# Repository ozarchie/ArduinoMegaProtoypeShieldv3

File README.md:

# ArduinoMegaProtoypeShieldv3
Arduino Mega protoype shield for loading HC05/WiFi modules
Welcome to the ArduinoMegaProtoypeShieldv3 wiki!

# Process
## Used proto_shield_MEGA-REV3 as the starting point
This is the reference schematic and layout from Arduino  
The target board is the arduino Mega2560v3 prototype shield usually supplied with a mini breadboard.  
It is similar to this item:  

I have no relationship with www.robotistan.com  

## Used Eagle 770 to edit schematic and board

The schematic was derived from an actual board.    
The board layout was measured from an actual board.  

<b>There are many points at which errors can be introduced.  
This is NOT a production item and has not been tested.    
It is for experimentation and collaboration only.    
At some stage, it may be 'released' as a verified design.  </b>

## Used eagle2fritzing to create Fritzing part

The part was generated using the eagle2fritzing technique.
See   
https://github.com/fritzing/eagle2fritzing

The program was re-compiled on macOS Sierra and run from the command line.  
`./run.sh ~/Documents/workspace/fritzing-myparts/`

## Minor modification in Fritzing to create and export part

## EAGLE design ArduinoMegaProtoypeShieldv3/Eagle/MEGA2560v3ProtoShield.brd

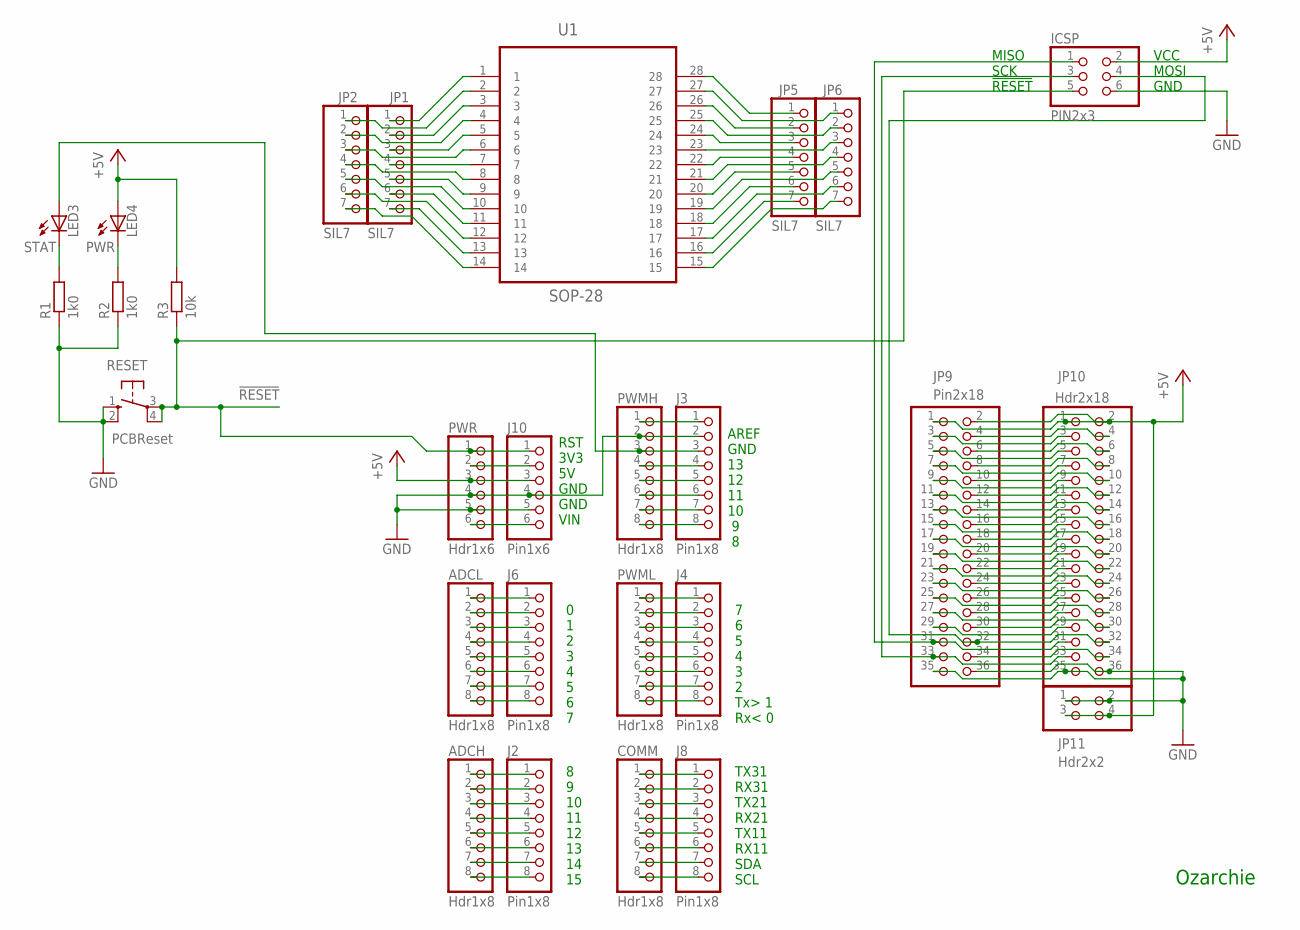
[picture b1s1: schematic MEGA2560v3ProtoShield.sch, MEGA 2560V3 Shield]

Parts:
ADCH: Hdr1x8; 1X08
ADCL: Hdr1x8; 1X08
COMM: Hdr1x8; 1X08
ICSP: PIN2x3; 2X03
J2, J3, J4, J6, J8: Pin1x8; 1X08
J10: Pin1x6; 1X06
JP1, JP2, JP5, JP6: SIL7; 1X07
JP9: Pin2x18; 2X18
JP10: Hdr2x18; 2X18
JP11: Hdr2x2; 2X02
LED3: STAT; CHIPLED_1206
LED4: PWR; CHIPLED_1206
PWMH: Hdr1x8; 1X08
PWML: Hdr1x8; 1X08
PWR: Hdr1x6; 1X06
R1, R2: 1k0; R0805
R3: 10k; R0805
RESET: PCBReset; B3F-10XX
U1: SOP-28; SOP50P1030X264-28N

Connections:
3V3: J10.2, PWR.2
!RESET!: ICSP.5, J10.1, PWR.1, R3.1, RESET.3, RESET.4 (P1)
+5V: ICSP.2, J10.3, JP9.1, JP9.2, JP10.1, JP10.2, JP11.3, JP11.4, LED4.A, PWR.3, R3.2
A0: ADCL.1, J6.1
A1: ADCL.2, J6.2
A2: ADCL.3, J6.3
A3: ADCL.4, J6.4
A4: ADCL.5, J6.5
A5: ADCL.6, J6.6
A6: ADCL.7, J6.7
A7: ADCL.8, J6.8
A8: ADCH.1, J2.1
A9: ADCH.2, J2.2
A10: ADCH.3, J2.3
A11: ADCH.4, J2.4
A12: ADCH.5, J2.5
A13: ADCH.6, J2.6
A14: ADCH.7, J2.7
A15: ADCH.8, J2.8
AREF: J3.1, PWMH.1
D0/RX0: J4.8, PWML.8
D1/TX0: J4.7, PWML.7
D2PWM: J4.6, PWML.6
D3PWM: J4.5, PWML.5
D4PWM: J4.4, PWML.4
D5PWM: J4.3, PWML.3
D6PWM: J4.2, PWML.2
D7PWM: J4.1, PWML.1
D8PWM: J3.8, PWMH.8
D9PWM: J3.7, PWMH.7
D10PWM: J3.6, PWMH.6
D11PWM: J3.5, PWMH.5
D12PWM: J3.4, PWMH.4
D13PWM: J3.3, LED3.A, PWMH.3
D14/TX3: COMM.1, J8.1
D15/RX3: COMM.2, J8.2
D16/TX2: COMM.3, J8.3
D17/RX2: COMM.4, J8.4
D18/TX1: COMM.5, J8.5
D19/RX1: COMM.6, J8.6
D20/SDA: COMM.7, J8.7
D21/SCL: COMM.8, J8.8
D22: JP9.3, JP10.3
D23: JP9.4, JP10.4
D24: JP9.5, JP10.5
D25: JP9.6, JP10.6
D26: JP9.7, JP10.7
D27: JP9.8, JP10.8
D28: JP9.9, JP10.9
D29: JP9.10, JP10.10
D30: JP9.11, JP10.11
D31: JP9.12, JP10.12
D32: JP9.13, JP10.13
D33: JP9.14, JP10.14
D34: JP9.15, JP10.15
D35: JP9.16, JP10.16
D36: JP9.17, JP10.17
D37: JP9.18, JP10.18
D38: JP9.19, JP10.19
D39: JP9.20, JP10.20
D40: JP9.21, JP10.21
D41: JP9.22, JP10.22
D42: JP9.23, JP10.23
D43: JP9.24, JP10.24
D44: JP9.25, JP10.25
D45: JP9.26, JP10.26
D46: JP9.27, JP10.27
D47: JP9.28, JP10.28
D48: JP9.29, JP10.29
D49: JP9.30, JP10.30
D53: JP9.34, JP10.34
GND: ICSP.6, J3.2, J10.4, J10.5, JP9.35, JP9.36, JP10.35, JP10.36, JP11.1, JP11.2, PWMH.2, PWR.4, PWR.5, R1.1, R2.1, RESET.1 (S), RESET.2 (S1)
MISO: ICSP.1, JP9.31, JP10.31
MOSI: ICSP.4, JP9.32, JP10.32
unnamed: LED3.C, R1.2
unnamed: LED4.C, R2.2
SCK: ICSP.3, JP9.33, JP10.33
SO1: JP1.1, U1.1
SO2: JP2.1, U1.2
SO3: JP1.2, U1.3
SO4: JP2.2, U1.4
SO5: JP1.3, U1.5
SO6: JP2.3, U1.6
SO7: JP1.4, U1.7
SO8: JP2.4, U1.8
SO9: JP1.5, U1.9
SO10: JP2.5, U1.10
SO11: JP1.6, U1.11
SO12: JP2.6, U1.12
SO13: JP1.7, U1.13
SO14: JP2.7, U1.14
SO15: JP6.7, U1.15
SO16: JP5.7, U1.16
SO17: JP6.6, U1.17
SO18: JP5.6, U1.18
SO19: JP6.5, U1.19
SO20: JP5.5, U1.20
SO21: JP6.4, U1.21
SO22: JP5.4, U1.22
SO23: JP6.3, U1.23
SO24: JP5.3, U1.24
SO25: JP6.2, U1.25
SO26: JP5.2, U1.26
SO27: JP6.1, U1.27
SO28: JP5.1, U1.28
VIN: J10.6, PWR.6

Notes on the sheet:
RST 3V3 5V GND GND VIN
MISO SCK !RESET!
VCC MOSI GND
AREF GND 13 12 11 10 9 8
7 6 5 4 3 2 Tx> 1 Rx< 0
0 1 2 3 4 5 6 7
8 9 10 11 12 13 14 15
TX31 RX31 TX21 RX21 TX11 RX11 SDA SCL
Ozarchie

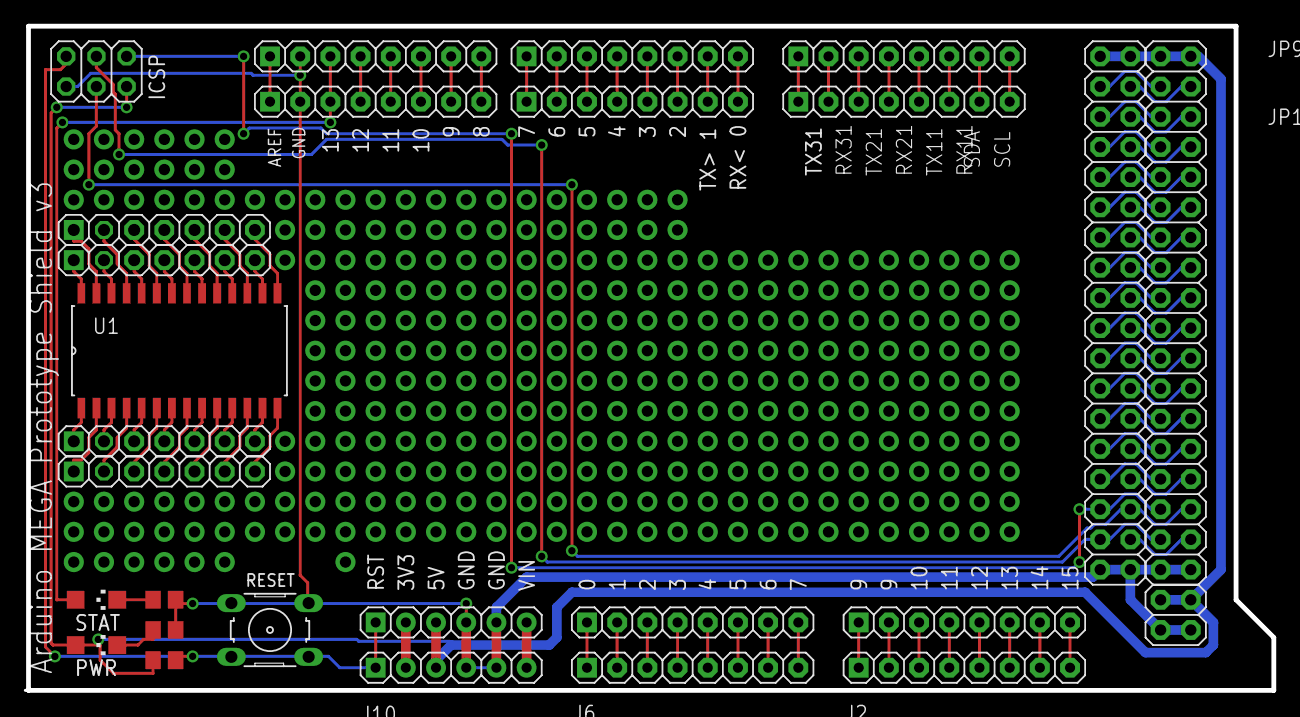
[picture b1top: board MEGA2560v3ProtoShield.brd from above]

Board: 2 copper layers, 104.8 x 55.9 mm, 27 parts (0 on the bottom side), 106 nets.

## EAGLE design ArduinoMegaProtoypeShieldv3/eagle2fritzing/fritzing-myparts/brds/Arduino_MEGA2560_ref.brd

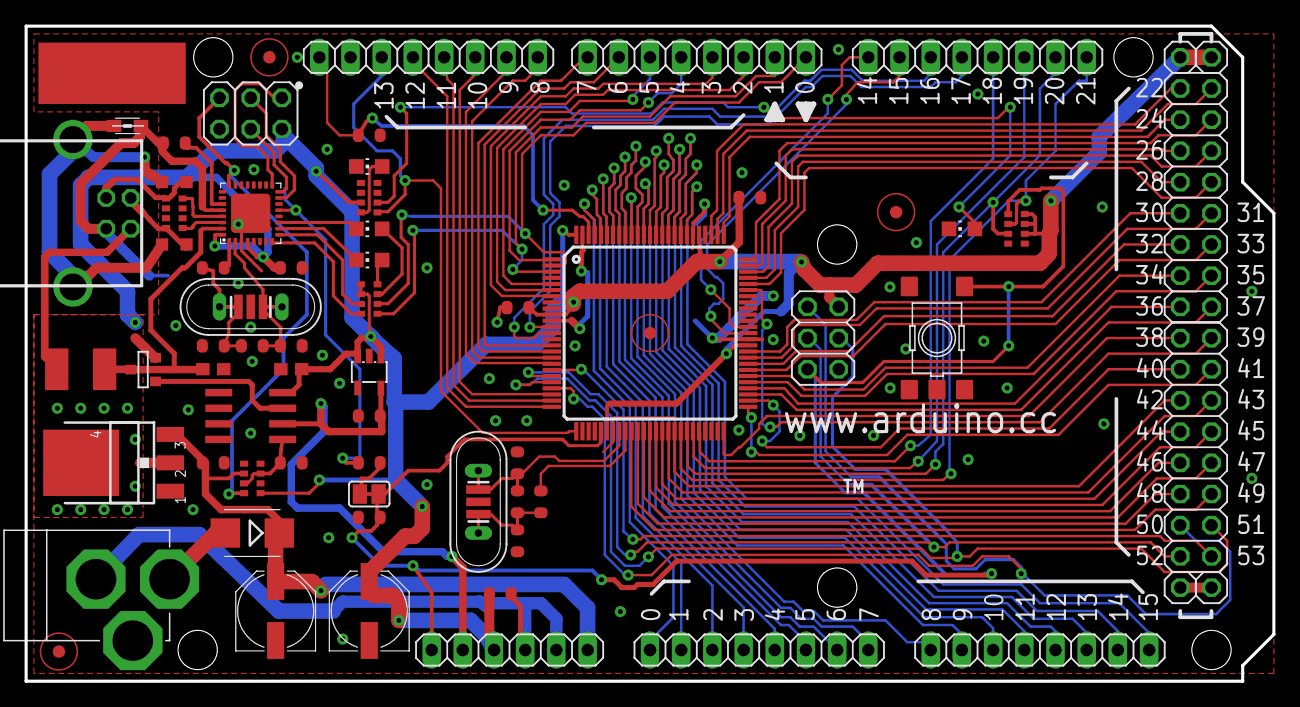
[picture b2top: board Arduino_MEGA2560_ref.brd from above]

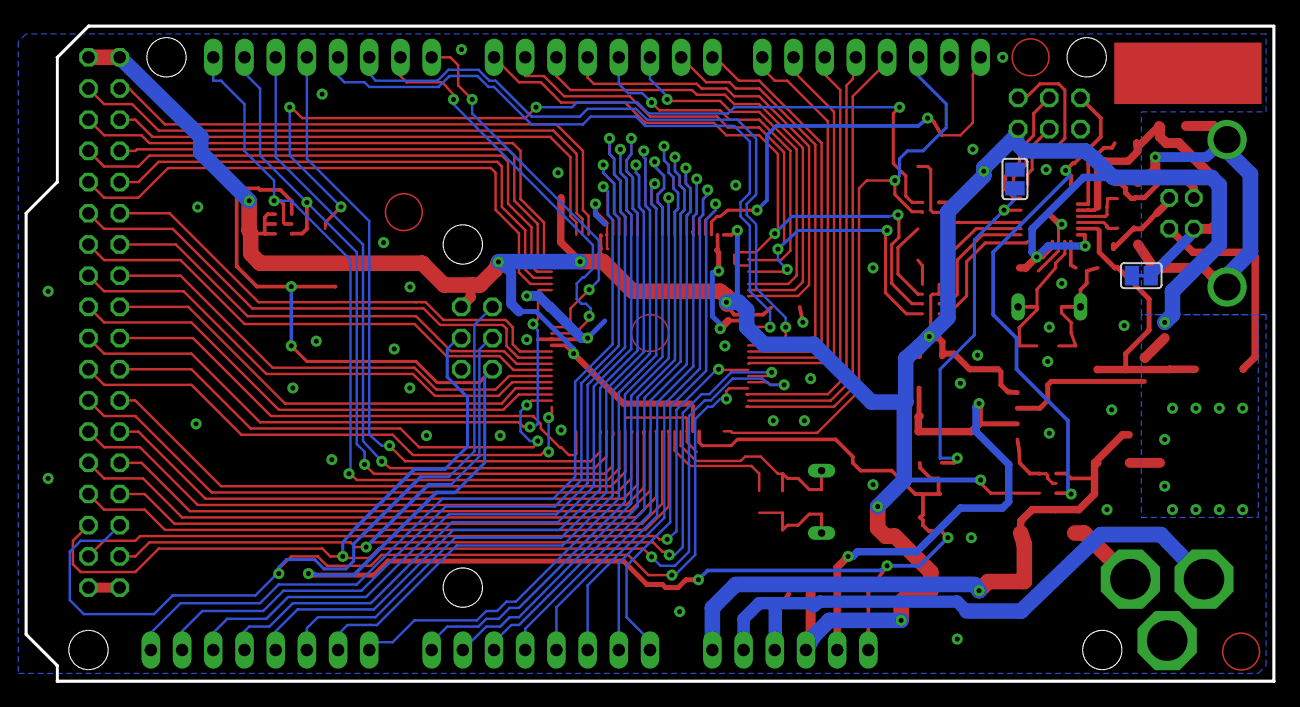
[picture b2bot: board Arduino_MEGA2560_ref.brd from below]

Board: 2 copper layers, 101.6 x 53.3 mm, 72 parts (2 on the bottom side), 107 nets.

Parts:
ADCH: 1X08
ADCL: 1X08
C1, C14, C15, C16, C17: 22p; C0603-ROUND
C2, C3, C4, C5, C6, C7, C9, C12, C13: 100n; C0603-ROUND
C8, C11: 100n; C0603
C10: 1u; C0603-ROUND
COMMUNICATION: 1X08
D1: M7; SMB
F1: 500mA; L1812
GROUND: SJ
IC1: MC33269ST-5.0T3; SOT223
IC2: MC33269D-5.0; DPACK
IC3: ATMEGA2560-16AU; TQFP100
IC4: ATMEGA8U2-MU; QFN32
IC5: LM358D; SO08
IC6: LP2985-33DBVR; SOT23-DBV
ICSP, ICSP1: ICSP; 2X03
JP1, JP2, JP3, JP4: 1X01
L: YELLOW; CHIP-LED0805
L1: BLM21; 0805
ON: GREEN; CHIP-LED0805
PC1, PC2: 47u; PANASONIC_D
POWER: 1X06
PWMH: 1X08
PWML: 1X08
Q1, Q2: 16MHz; QS
R1, R2: 1M; R0603-ROUND
R3, R4: 27R; R0603-ROUND
RESET: TS42
RESET-EN: SJ
RN1, RN5: 10K; CAT16
RN2: 22R; CAY16
RN3, RN4: 1k; CAY16
RX: YELLOW; CHIP-LED0805
T2: FDN340P; SOT-23
TX: YELLOW; CHIP-LED0805
U$2, U$3, U$4, U$5: FIDUCIALMOUNT; FIDUCIA-MOUNT
UBOOT: SJ
X1: DC21MMX; DC-21MM
X2: PN61729
XIOH: 2X08
XIOL: 2X08
Y1, Y2: 16MHz; RESONATOR
Z1, Z2: PGB1010604; CT/CN0603

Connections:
+3V3: C13.2, IC5.6, IC6.5, POWER.2
+5V: C4.1, C5.1, C6.1, C9.1, C11.2, IC1.2, IC1.4, IC2.2, IC3.10, IC3.31, IC3.61, IC3.80, IC3.100, IC4.4, IC4.32, IC5.8, IC6.1, IC6.3, ICSP.2, ICSP1.2, JP1.1, JP2.1, PC2.+, POWER.3, RN1.6, RN1.7, RN1.8, RN3.3, RN4.5, RN4.6, RN5.1, T2.2
ADC0: ADCL.1, IC3.97
ADC1: ADCL.2, IC3.96
ADC2: ADCL.3, IC3.95
ADC3: ADCL.4, IC3.94
ADC4: ADCL.5, IC3.93
ADC5: ADCL.6, IC3.92
ADC6: ADCL.7, IC3.91
ADC7: ADCL.8, IC3.90
ADC8: ADCH.1, IC3.89
ADC9: ADCH.2, IC3.88
ADC10: ADCH.3, IC3.87
ADC11: ADCH.4, IC3.86
ADC12: ADCH.5, IC3.85
ADC13: ADCH.6, IC3.84
ADC14: ADCH.7, IC3.83
ADC15: ADCH.8, IC3.82
AREF: C3.1, IC3.98, PWMH.8
CMP: C12.2, IC5.5, RN5.3, RN5.7
D+: RN2.5, X2.3, Z2.2
D-: RN2.8, X2.2, Z1.2
DTR: C7.1, IC4.13, UBOOT.1
GATE_CMD: IC5.7, T2.3
GND: C1.2, C2.2, C3.2, C4.2, C5.2, C6.2, C8.2, C9.2, C11.1, C12.1, C13.1, C14.1, C15.1, C16.2, C17.2, GROUND.2, IC1.1, IC2.1, IC3.11, IC3.32, IC3.62, IC3.81, IC3.99, IC4.3, IC4.EXP, IC5.2, IC5.3, IC5.4, IC6.2, ICSP.6, ICSP1.6, JP3.1, JP4.1, L.C, ON.C, PC1.-, PC2.-, POWER.4, POWER.5, PWMH.7, RESET.1, RESET.2, RN5.2, UBOOT.2, X1.1, X1.3, Y1.2, Y2.2
M8RXD: IC4.9, RN4.7
M8TXD: IC4.8, RN4.8
MISO2: IC4.17, ICSP1.1
MOSI2: IC4.16, ICSP1.4
unnamed: L.A, RN3.4
unnamed: ON.A, RN3.6
unnamed: RN4.4, RX.A
unnamed: RN4.3, TX.A
PA0: IC3.78, XIOH.16
PA1: IC3.77, XIOH.15
PA2: IC3.76, XIOH.14
PA3: IC3.75, XIOH.13
PA4: IC3.74, XIOH.12
PA5: IC3.73, XIOH.11
PA6: IC3.72, XIOH.10
PA7: IC3.71, XIOH.9
PB0: IC3.19, XIOL.1
PB1: IC3.20, ICSP.3, XIOL.2
PB2: IC3.21, ICSP.4, XIOL.3
PB3: IC3.22, ICSP.1, XIOL.4
PB4: IC3.23, PWMH.3
PB5: IC3.24, PWMH.4
PB6: IC3.25, PWMH.5
PB7: IC3.26, PWMH.6, RN3.5
PC0: IC3.53, XIOH.1
PC1: IC3.54, XIOH.2
PC2: IC3.55, XIOH.3
PC3: IC3.56, XIOH.4
PC4: IC3.57, XIOH.5
PC5: IC3.58, XIOH.6
PC6: IC3.59, XIOH.7
PC7: IC3.60, XIOH.8
PD7: IC3.50, XIOL.16
PE0: IC3.2, PWML.1, RN4.2
PE1: IC3.3, PWML.2, RN4.1
PE3: IC3.5, PWML.6
PE4: IC3.6, PWML.3
PE5: IC3.7, PWML.4
PG0: IC3.51, XIOL.13
PG1: IC3.52, XIOL.14
PG2: IC3.70, XIOL.15
PG5: IC3.1, PWML.5
PH3: IC3.15, PWML.7
PH4: IC3.16, PWML.8
PH5: IC3.17, PWMH.1
PH6: IC3.18, PWMH.2
PL0: IC3.35, XIOL.5
PL1: IC3.36, XIOL.6
PL2: IC3.37, XIOL.7
PL3: IC3.38, XIOL.8
PL4: IC3.39, XIOL.9
PL5: IC3.40, XIOL.10
PL6: IC3.41, XIOL.11
PL7: IC3.42, XIOL.12
PWRIN: D1.A, X1.2
RD+: IC4.29, RN2.4
RD-: IC4.30, RN2.1
RESET: C1.1, C7.2, IC3.30, ICSP.5, POWER.1, RESET.3, RESET.4, RESET-EN.1, RESET-EN.2, RN1.1
RESET2: IC4.24, ICSP1.5, RN5.8
RXD1: COMMUNICATION.3, IC3.45
RXD2: COMMUNICATION.5, IC3.12
RXD3: COMMUNICATION.7, IC3.63
RXL: IC4.10, RX.C
SCK2: IC4.15, ICSP1.3
SCL: COMMUNICATION.1, IC3.43, RN1.2
SDA: COMMUNICATION.2, IC3.44, RN1.3
TXD1: COMMUNICATION.4, IC3.46
TXD2: COMMUNICATION.6, IC3.13
TXD3: COMMUNICATION.8, IC3.64
TXL: IC4.11, TX.C
UGND: C10.2, GROUND.1, IC4.28, L1.1, X2.4
USBVCC: C8.1, F1.1, IC4.31, T2.1
USHIELD: L1.2, X2.P$1, X2.P$2, Z1.1, Z2.1
VIN: C2.1, D1.C, IC1.3, IC2.3, PC1.+, POWER.6, RN5.6
VUCAP: C10.1, IC4.27
XT1: C16.1, Q1.2, R2.1, R4.2, Y2.3
XT1R: IC4.1, R4.1
XT2: C17.1, IC4.2, Q1.1, R2.2, Y2.1
XTAL1: C14.2, Q2.2, R1.1, R3.2, Y1.3
XTAL1R: IC3.34, R3.1
XTAL2: C15.2, IC3.33, Q2.1, R1.2, Y1.1
XVCC: F1.2, X2.1

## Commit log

2017-01-04 Initial files
2017-01-04 Set theme jekyll-theme-cayman

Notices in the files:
parts and their libraries:
pmc: Created by Ultra Librarian Gold 5.3.88 Copyright © 1999-2010
